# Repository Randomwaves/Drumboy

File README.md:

# Drumboy

**A touch-controlled hardware groovebox** — sequencer, sampler, and DSP effects engine built around an STM32H723 (Cortex-M7), with a 480×854 color display, a fully capacitive-touch control surface, and MIDI/Sync I/O.

This repository holds the complete hardware design (Eagle/KiCad) and firmware (STM32CubeIDE / C++) for Drumboy, released by [Randomwaves](https://randomwaves.io) as an open hardware/software project. Drumboy is the predecessor of [Drumboy Pro](https://github.com/Randomwaves/Drumboy-Pro), sharing the same sequencer and DSP engine on a simpler, touch-based control surface.

---

## Overview

The MCU sits at the center of the same core subsystems as Drumboy Pro: an NT35510 display over a 16-bit parallel GPIO bus, external SDRAM on the FMC bus for sample streaming, an SGTL5000 audio codec over I2S/I2C, a microSD card over SDMMC2 for storage, and MIDI/Sync connectivity over USART/GPIO. In place of mechanical keys and encoders, the control surface is driven entirely by three capacitive-touch channels.

| | |
|---|---|
| **MCU** | STM32H723ZGT6 — Cortex-M7, LQFP-144 |
| **Display** | NT35510, 480×854, 16-bit parallel |
| **SDRAM** | External, FMC bus (sample streaming) |
| **Audio codec** | SGTL5000 — I2S3 audio / I2C3 control |
| **Storage** | microSD, SDMMC2, FAT filesystem |
| **Control surface** | 3× capacitive-touch channels (CT0–CT2) |
| **Connectivity** | MIDI In/Out, Sync In/Out |
| **Firmware** | v1.05 |

## Features

- **10 sample layers**, each with independent LFO-driven modulation
- **Sequencer** with 5 song banks per layer, 64 beats per bank, and algorithmic complex-fill generation (12 sub-hits per fill slot)
- **9 effect types** per send slot: Delay, Chorus, Flanger, Phaser, Compressor, Expander, Overdrive, Distortion, Bitcrusher
- **2 multimode filters + 2 send effects + stereo reverb** in the DSP chain
- **MIDI In/Out** and **Sync In/Out** for external clock/gate sync
- **SD-card firmware updates** via a dedicated bootloader, mirroring the same two-project split as Drumboy Pro

## Repository structure

```
01 Hardware/
  Main/       Main board — Eagle CAD (Main.sch / Main.brd)
  Top/        Top/control-surface board — Eagle CAD (Top.sch / Top.brd)
  Connector/  Interconnect board — KiCad (migrated from Eagle)
  Bottom/     Base board — KiCad (migrated from Eagle)

02 Software/
  Drumboy-Boot-H723/   Bootloader — STM32CubeIDE project
  Drumboy-App-H723/    Application firmware — STM32CubeIDE project
  Firmware/            Prebuilt firmware binaries
  Sd Card/             Reference SD card contents (samples, presets, drumkits, system data)
```

## Hardware

Main and Top were originally designed in **Autodesk Eagle** (`.sch` / `.brd`); Connector and Bottom have since been migrated to **KiCad**.

## Firmware

Built with **STM32CubeIDE**, written in C/C++ against the STM32 HAL. Firmware is split into `Drumboy-Boot-H723` (bootloader) and `Drumboy-App-H723` (application), sharing one flash device — the same split used in Drumboy Pro.

## License

Released under the [MIT License](LICENSE).

## Community

- 💬 [Discord community](https://discord.gg/5atevNH6UU) — join the discussion
- 🌐 [randomwaves.io](https://www.randomwaves.io)
- ✉️ [hello@randomwaves.io](mailto:hello@randomwaves.io)

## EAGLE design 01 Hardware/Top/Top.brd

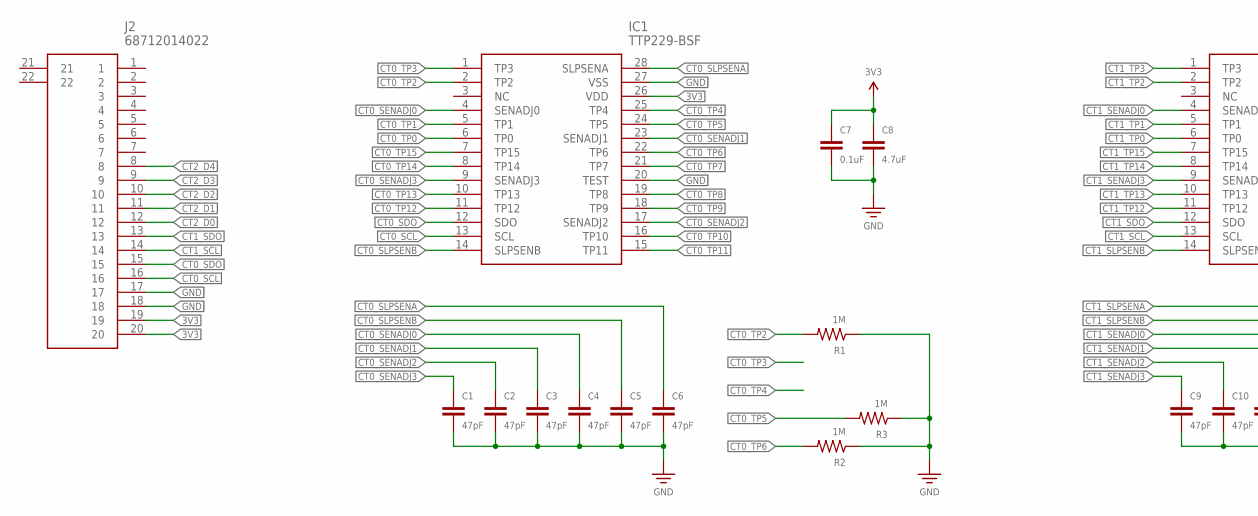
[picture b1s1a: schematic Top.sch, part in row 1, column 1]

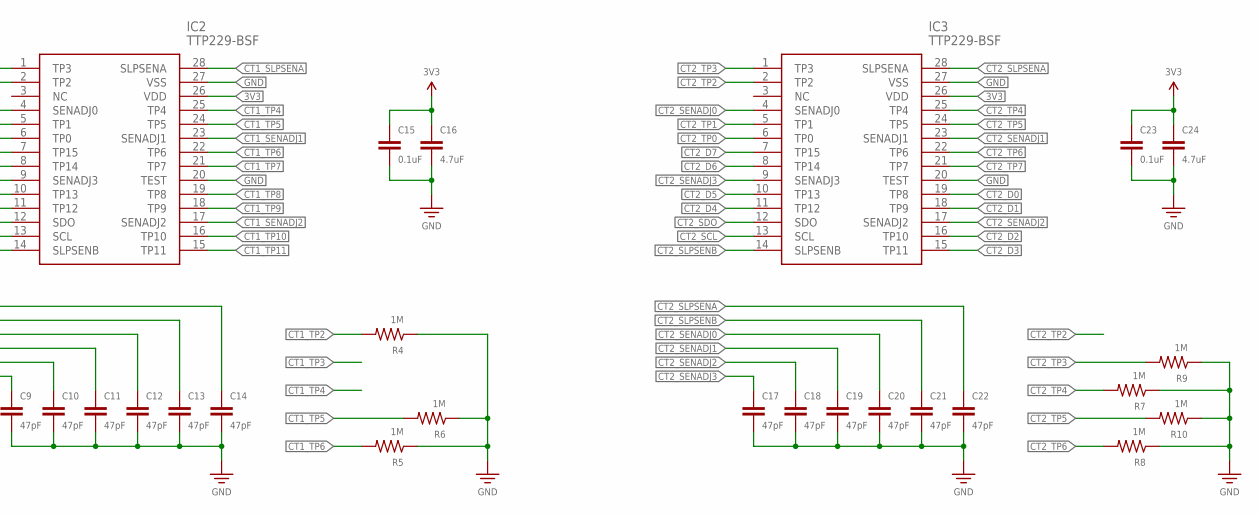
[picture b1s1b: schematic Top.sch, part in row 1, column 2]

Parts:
C1, C2, C3, C4, C5, C6, C9, C10, C11, C12, C13, C14, C17, C18, C19, C20, C21, C22: 47pF; CAP-0603
C7, C15, C23: 0.1uF; CAP-0603
C8, C16, C24: 4.7uF; CAP-0603
IC1, IC2, IC3: TTP229-BSF; SOP64P600X175-28N
J2: 68712014022
R1, R2, R3, R4, R5, R6, R7, R8, R9, R10: 1M; RES-0603

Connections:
3V3: C7.P$1 (1), C8.P$1 (1), C15.P$1 (1), C16.P$1 (1), C23.P$1 (1), C24.P$1 (1), IC1.26 (VDD), IC2.26 (VDD), IC3.26 (VDD), J2.19, J2.20
CT0_SCL: IC1.13 (SCL), J2.16
CT0_SDO: IC1.12 (SDO), J2.15
CT0_SENADJ0: C4.P$1 (1), IC1.4 (SENADJ0)
CT0_SENADJ1: C3.P$1 (1), IC1.23 (SENADJ1)
CT0_SENADJ2: C2.P$1 (1), IC1.17 (SENADJ2)
CT0_SENADJ3: C1.P$1 (1), IC1.9 (SENADJ3)
CT0_SLPSENA: C6.P$1 (1), IC1.28 (SLPSENA)
CT0_SLPSENB: C5.P$1 (1), IC1.14 (SLPSENB)
CT0_TP0: IC1.6 (TP0)
CT0_TP1: IC1.5 (TP1)
CT0_TP2: IC1.2 (TP2), R1.P$2 (2)
CT0_TP3: IC1.1 (TP3)
CT0_TP4: IC1.25 (TP4)
CT0_TP5: IC1.24 (TP5), R3.P$2 (2)
CT0_TP6: IC1.22 (TP6), R2.P$2 (2)
CT0_TP7: IC1.21 (TP7)
CT0_TP8: IC1.19 (TP8)
CT0_TP9: IC1.18 (TP9)
CT0_TP10: IC1.16 (TP10)
CT0_TP11: IC1.15 (TP11)
CT0_TP12: IC1.11 (TP12)
CT0_TP13: IC1.10 (TP13)
CT0_TP14: IC1.8 (TP14)
CT0_TP15: IC1.7 (TP15)
CT1_SCL: IC2.13 (SCL), J2.14
CT1_SDO: IC2.12 (SDO), J2.13
CT1_SENADJ0: C12.P$1 (1), IC2.4 (SENADJ0)
CT1_SENADJ1: C11.P$1 (1), IC2.23 (SENADJ1)
CT1_SENADJ2: C10.P$1 (1), IC2.17 (SENADJ2)
CT1_SENADJ3: C9.P$1 (1), IC2.9 (SENADJ3)
CT1_SLPSENA: C14.P$1 (1), IC2.28 (SLPSENA)
CT1_SLPSENB: C13.P$1 (1), IC2.14 (SLPSENB)
CT1_TP0: IC2.6 (TP0)
CT1_TP1: IC2.5 (TP1)
CT1_TP2: IC2.2 (TP2), R4.P$2 (2)
CT1_TP3: IC2.1 (TP3)
CT1_TP4: IC2.25 (TP4)
CT1_TP5: IC2.24 (TP5), R6.P$2 (2)
CT1_TP6: IC2.22 (TP6), R5.P$2 (2)
CT1_TP7: IC2.21 (TP7)
CT1_TP8: IC2.19 (TP8)
CT1_TP9: IC2.18 (TP9)
CT1_TP10: IC2.16 (TP10)
CT1_TP11: IC2.15 (TP11)
CT1_TP12: IC2.11 (TP12)
CT1_TP13: IC2.10 (TP13)
CT1_TP14: IC2.8 (TP14)
CT1_TP15: IC2.7 (TP15)
CT2_D0: IC3.19 (TP8), J2.12
CT2_D1: IC3.18 (TP9), J2.11
CT2_D2: IC3.16 (TP10), J2.10
CT2_D3: IC3.15 (TP11), J2.9
CT2_D4: IC3.11 (TP12), J2.8
CT2_D5: IC3.10 (TP13)
CT2_D6: IC3.8 (TP14)
CT2_D7: IC3.7 (TP15)
CT2_SCL: IC3.13 (SCL)
CT2_SDO: IC3.12 (SDO)
CT2_SENADJ0: C20.P$1 (1), IC3.4 (SENADJ0)
CT2_SENADJ1: C19.P$1 (1), IC3.23 (SENADJ1)
CT2_SENADJ2: C18.P$1 (1), IC3.17 (SENADJ2)
CT2_SENADJ3: C17.P$1 (1), IC3.9 (SENADJ3)
CT2_SLPSENA: C22.P$1 (1), IC3.28 (SLPSENA)
CT2_SLPSENB: C21.P$1 (1), IC3.14 (SLPSENB)
CT2_TP0: IC3.6 (TP0)
CT2_TP1: IC3.5 (TP1)
CT2_TP2: IC3.2 (TP2)
CT2_TP3: IC3.1 (TP3), R9.P$2 (2)
CT2_TP4: IC3.25 (TP4), R7.P$2 (2)
CT2_TP5: IC3.24 (TP5), R10.P$2 (2)
CT2_TP6: IC3.22 (TP6), R8.P$2 (2)
CT2_TP7: IC3.21 (TP7)
GND: C1.P$2 (2), C2.P$2 (2), C3.P$2 (2), C4.P$2 (2), C5.P$2 (2), C6.P$2 (2), C7.P$2 (2), C8.P$2 (2), C9.P$2 (2), C10.P$2 (2), C11.P$2 (2), C12.P$2 (2), C13.P$2 (2), C14.P$2 (2), C15.P$2 (2), C16.P$2 (2), C17.P$2 (2), C18.P$2 (2), C19.P$2 (2), C20.P$2 (2), C21.P$2 (2), C22.P$2 (2), C23.P$2 (2), C24.P$2 (2), IC1.20 (TEST), IC1.27 (VSS), IC2.20 (TEST), IC2.27 (VSS), IC3.20 (TEST), IC3.27 (VSS), J2.17, J2.18, R1.P$1 (1), R2.P$1 (1), R3.P$1 (1), R4.P$1 (1), R5.P$1 (1), R6.P$1 (1), R7.P$1 (1), R8.P$1 (1), R9.P$1 (1), R10.P$1 (1)

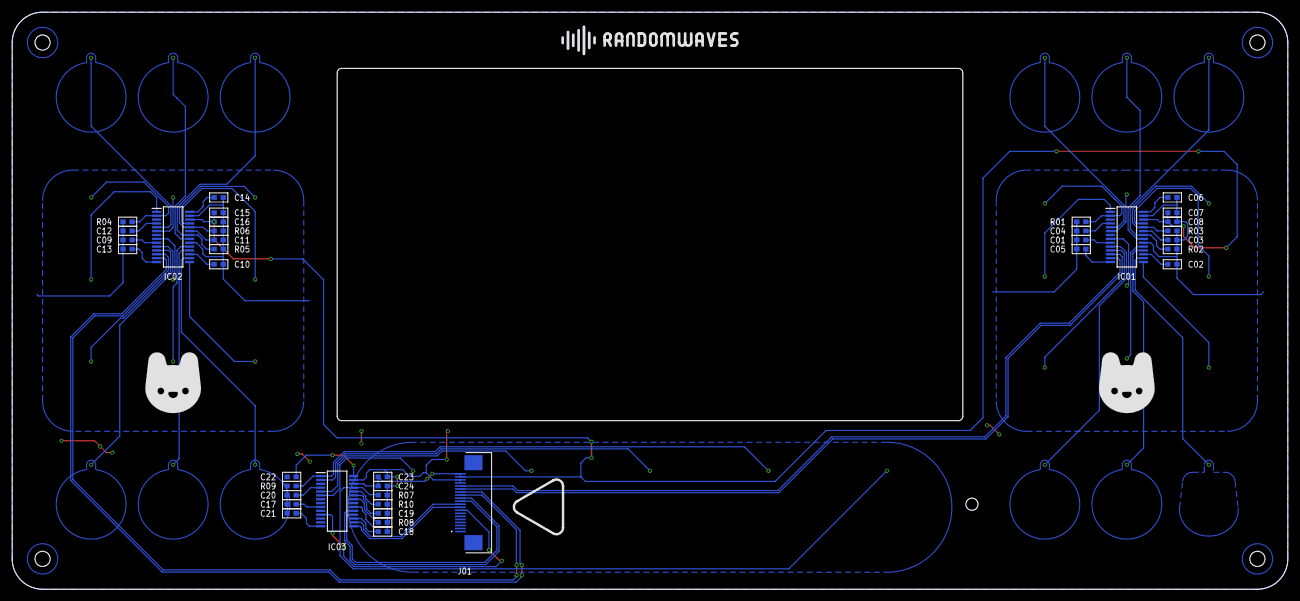
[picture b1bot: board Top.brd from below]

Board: 2 copper layers, 210.0 x 95.0 mm, 38 parts (38 on the bottom side), 39 nets.

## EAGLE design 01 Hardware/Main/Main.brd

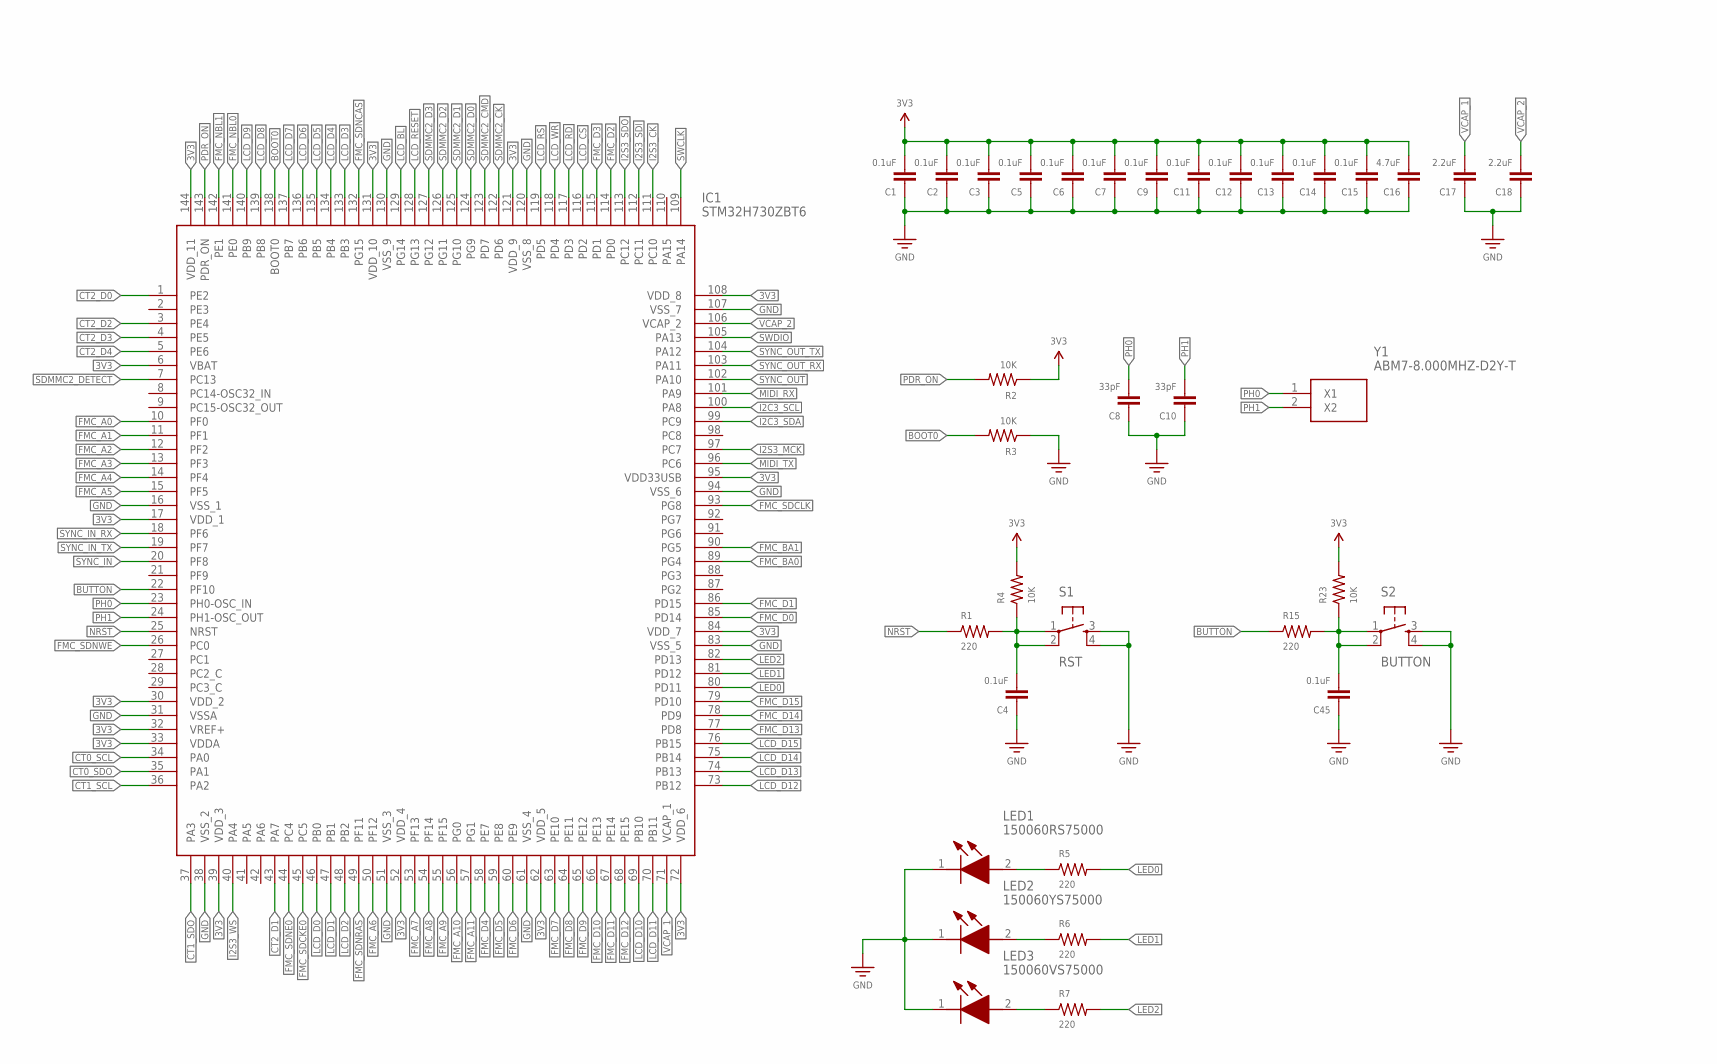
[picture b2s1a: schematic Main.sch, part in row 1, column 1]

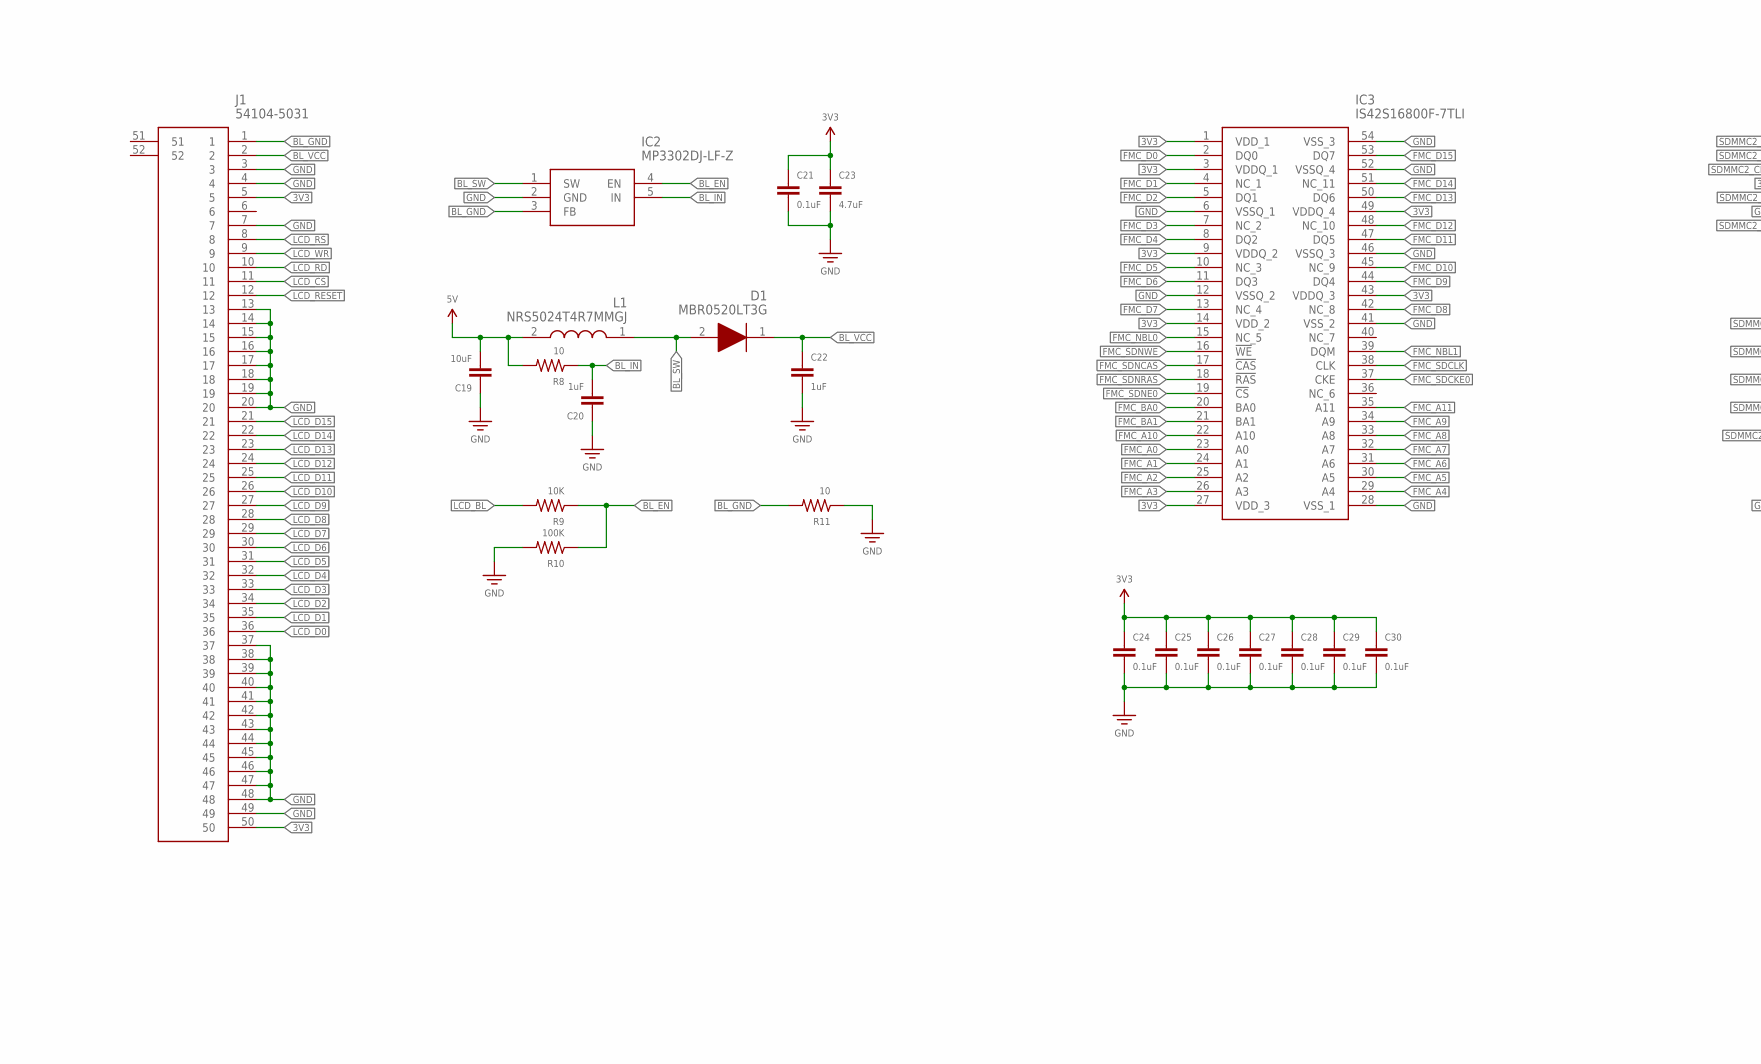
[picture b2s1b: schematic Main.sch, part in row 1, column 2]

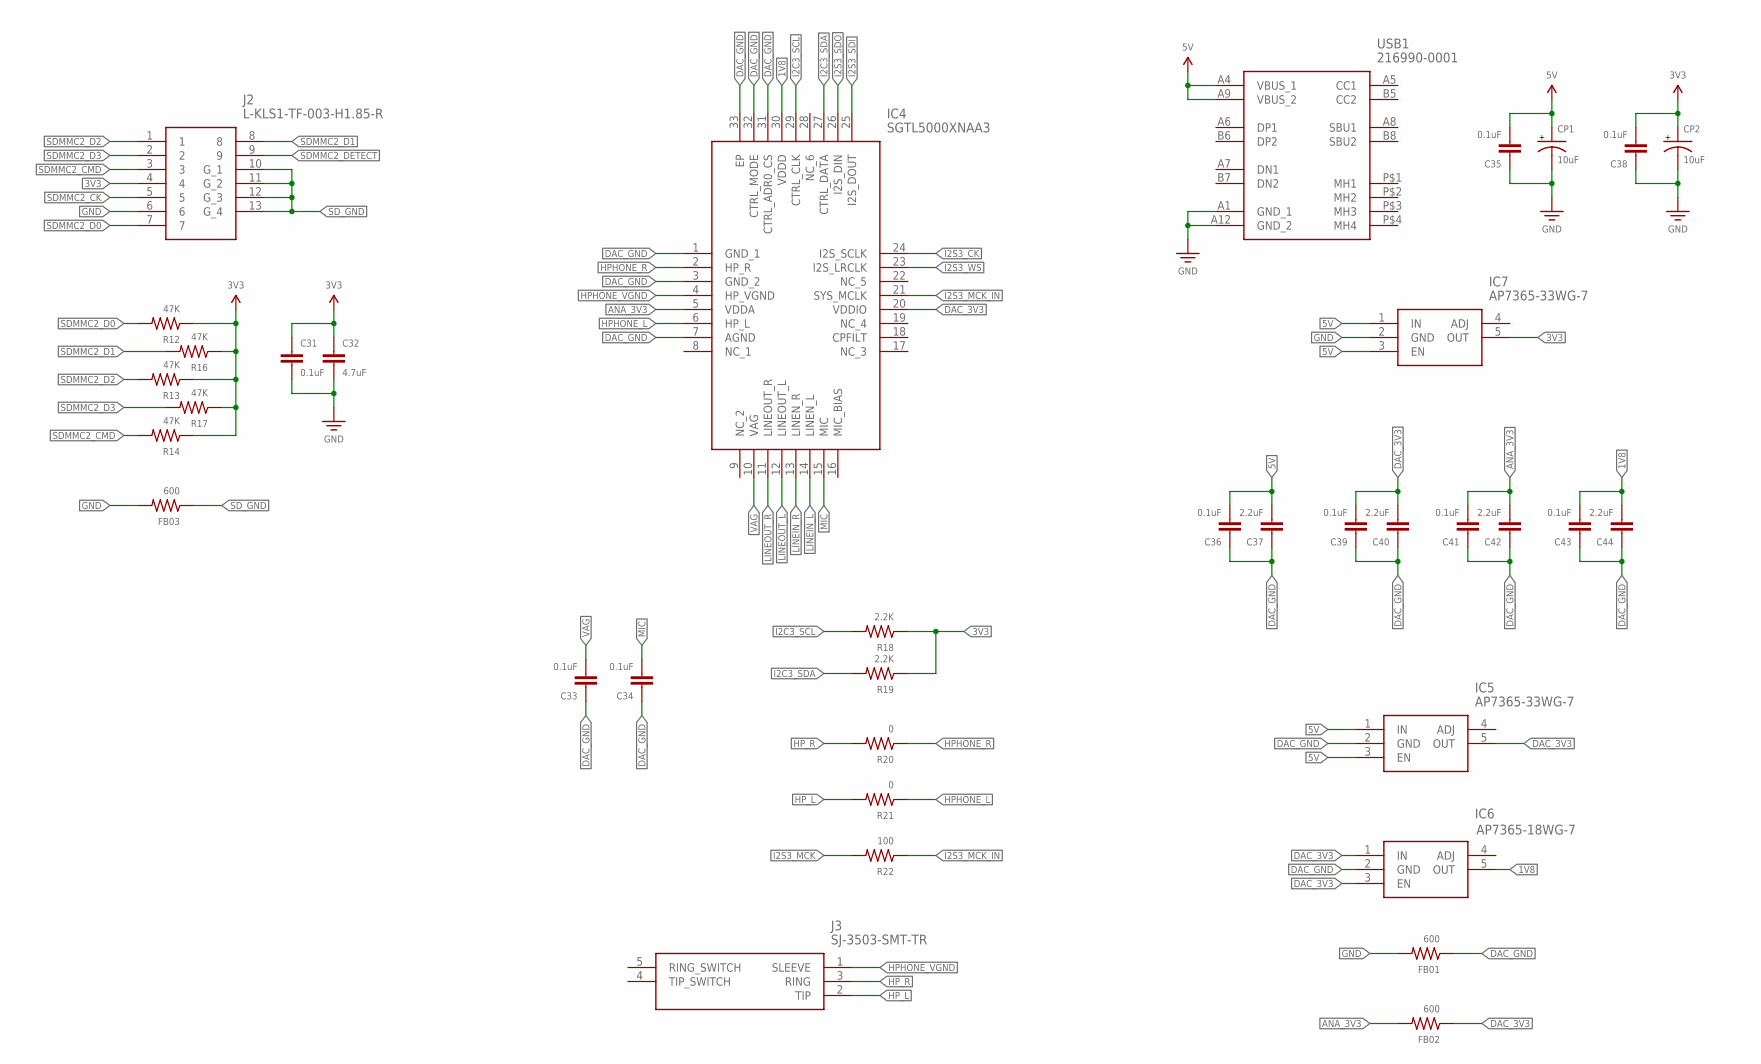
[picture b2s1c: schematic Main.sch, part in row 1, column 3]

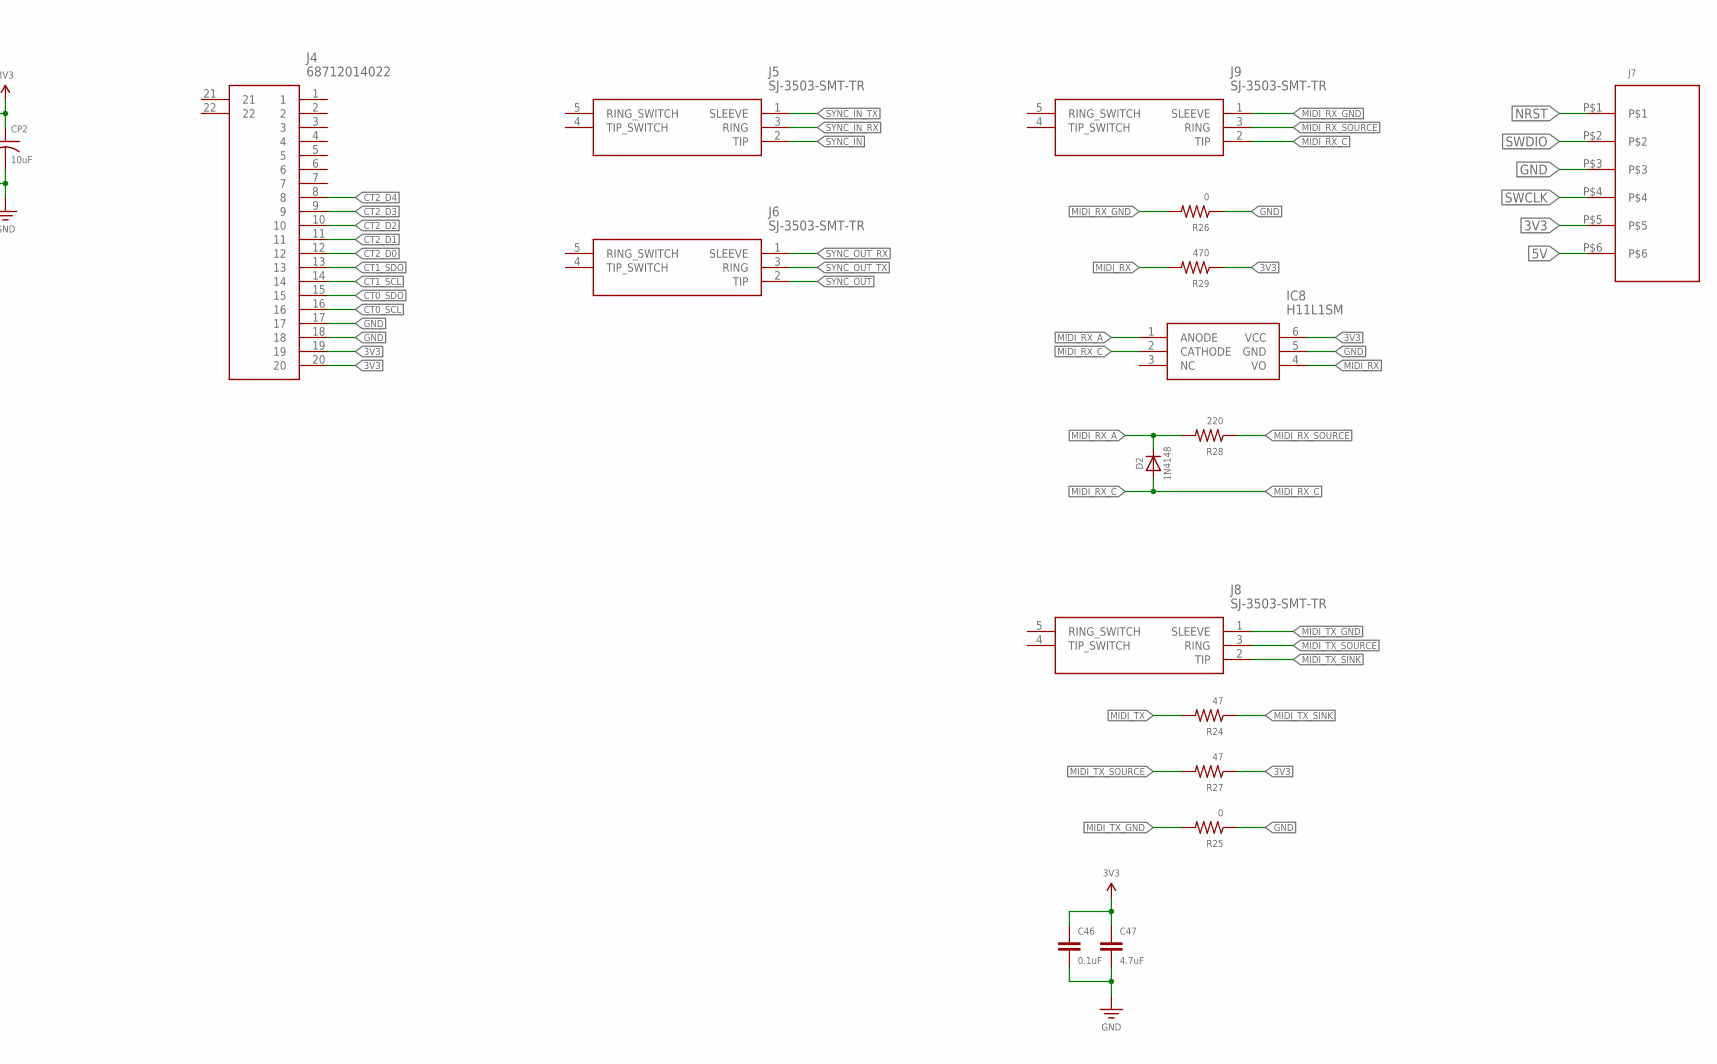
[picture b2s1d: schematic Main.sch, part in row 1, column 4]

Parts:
C1, C2, C3, C4, C5, C6, C7, C9, C11, C12, C13, C14, C15, C21, C24, C25, C26, C27, C28, C29, C30, C31, C33, C34, C35, C36, C38, C39, C41, C43, C45, C46: 0.1uF; CAP-0603
C8, C10: 33pF; CAP-0603
C16, C23, C32, C47: 4.7uF; CAP-0603
C17, C18, C37, C40, C42, C44: 2.2uF; CAP-0603
C19: 10uF; CAP-0603
C20, C22: 1uF; CAP-0603
CP1, CP2: 10uF; CAP-POL-1206
D1: MBR0520LT3G; SOD3716X135N
D2: 1N4148; SOD-323
FB01, FB02, FB03: 600; RES-0603
IC1: STM32H730ZBT6; QFP50P2200X2200X160-144N
IC2: MP3302DJ-LF-Z; SOT95P280X100-5N
IC3: IS42S16800F-7TLI; SOP80P1176X120-54N
IC4: SGTL5000XNAA3; QFN50P500X500X90-33N
IC5, IC7: AP7365-33WG-7; SOT95P285X130-5N
IC6: AP7365-18WG-7; SOT95P285X130-5N
IC8: H11L1SM; SMT-6PIN-(LEAD-BEND)
J1: 54104-5031; 541045031
J2: L-KLS1-TF-003-H1.85-R
J3, J5, J6, J8, J9: SJ-3503-SMT-TR; SJ3503SMTTR
J4: 68712014022
J7: HFW6R-2STE1LF
L1: NRS5024T4R7MMGJ
LED1: 150060RS75000; LEDC1608X80N
LED2: 150060YS75000; LEDC1608X80N
LED3: 150060VS75000; LEDC1608X80N
R1, R5, R6, R7, R15, R28: 220; RES-0603
R2, R3, R4, R9, R23: 10K; RES-0603
R8, R11: 10; RES-0603
R10: 100K; RES-0603
R12, R13, R14, R16, R17: 47K; RES-0603
R18, R19: 2.2K; RES-0603
R20, R21, R25, R26: 0; RES-0603
R22: 100; RES-0603
R24, R27: 47; RES-0603
R29: 470; RES-0603
S1: RST; TACTILE-SWITCH-SMD
S2: BUTTON; TACTILE-SWITCH-SMD
USB1: 216990-0001; 2169900001
Y1: ABM7-8.000MHZ-D2Y-T; ABM78000MHZD2YT

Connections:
1V8: C43.P$2 (2), C44.P$2 (2), IC4.30 (VDDD), IC6.5 (OUT)
3V3: C1.P$2 (2), C2.P$2 (2), C3.P$2 (2), C5.P$2 (2), C6.P$2 (2), C7.P$2 (2), C9.P$2 (2), C11.P$2 (2), C12.P$2 (2), C13.P$2 (2), C14.P$2 (2), C15.P$2 (2), C16.P$2 (2), C21.P$1 (1), C23.P$1 (1), C24.P$1 (1), C25.P$1 (1), C26.P$1 (1), C27.P$1 (1), C28.P$1 (1), C29.P$1 (1), C30.P$1 (1), C31.P$1 (1), C32.P$1 (1), C38.P$2 (2), C46.P$1 (1), C47.P$1 (1), CP2.P$1 (+), IC1.6 (VBAT), IC1.17 (VDD_1), IC1.30 (VDD_2), IC1.32 (VREF+), IC1.33 (VDDA), IC1.39 (VDD_3), IC1.52 (VDD_4), IC1.62 (VDD_5), IC1.72 (VDD_6), IC1.84 (VDD_7), IC1.95 (VDD33USB), IC1.108 (VDD_8), IC1.121 (VDD_9), IC1.131 (VDD_10), IC1.144 (VDD_11), IC3.1 (VDD_1), IC3.3 (VDDQ_1), IC3.9 (VDDQ_2), IC3.14 (VDD_2), IC3.27 (VDD_3), IC3.43 (VDDQ_3), IC3.49 (VDDQ_4), IC7.5 (OUT), IC8.6 (VCC), J1.5, J1.50, J2.4, J4.19, J4.20, J7.P$5, R2.P$1 (1), R4.P$2 (2), R12.P$1 (1), R13.P$1 (1), R14.P$1 (1), R16.P$1 (1), R17.P$1 (1), R18.P$1 (1), R19.P$1 (1), R23.P$2 (2), R27.P$1 (1), R29.P$1 (1)
5V: C19.P$2 (2), C35.P$2 (2), C36.P$2 (2), C37.P$2 (2), CP1.P$1 (+), IC5.1 (IN), IC5.3 (EN), IC7.1 (IN), IC7.3 (EN), J7.P$6, L1.2, R8.P$2 (2), USB1.A4 (VBUS_1), USB1.A9 (VBUS_2)
ANA_3V3: C41.P$2 (2), C42.P$2 (2), FB02.P$2 (2), IC4.5 (VDDA)
BL_EN: IC2.4 (EN), R9.P$1 (1), R10.P$1 (1)
BL_GND: IC2.3 (FB), J1.1, R11.P$2 (2)
BL_IN: C20.P$2 (2), IC2.5 (IN), R8.P$1 (1)
BL_SW: D1.2 (A), IC2.1 (SW), L1.1
BL_VCC: C22.P$1 (1), D1.1 (K), J1.2
BOOT0: IC1.138 (BOOT0), R3.P$2 (2)
BUTTON: IC1.22 (PF10), R15.P$1 (1)
CT0_SCL: IC1.34 (PA0), J4.16
CT0_SDO: IC1.35 (PA1), J4.15
CT1_SCL: IC1.36 (PA2), J4.14
CT1_SDO: IC1.37 (PA3), J4.13
CT2_D0: IC1.1 (PE2), J4.12
CT2_D1: IC1.43 (PA7), J4.11
CT2_D2: IC1.3 (PE4), J4.10
CT2_D3: IC1.4 (PE5), J4.9
CT2_D4: IC1.5 (PE6), J4.8
DAC_3V3: C39.P$2 (2), C40.P$2 (2), FB02.P$1 (1), IC4.20 (VDDIO), IC5.5 (OUT), IC6.1 (IN), IC6.3 (EN)
DAC_GND: C33.P$1 (1), C34.P$1 (1), C36.P$1 (1), C37.P$1 (1), C39.P$1 (1), C40.P$1 (1), C41.P$1 (1), C42.P$1 (1), C43.P$1 (1), C44.P$1 (1), FB01.P$1 (1), IC4.1 (GND_1), IC4.3 (GND_2), IC4.7 (AGND), IC4.31 (CTRL_ADR0_CS), IC4.32 (CTRL_MODE), IC4.33 (EP), IC5.2 (GND), IC6.2 (GND)
FMC_A0: IC1.10 (PF0), IC3.23 (A0)
FMC_A1: IC1.11 (PF1), IC3.24 (A1)
FMC_A2: IC1.12 (PF2), IC3.25 (A2)
FMC_A3: IC1.13 (PF3), IC3.26 (A3)
FMC_A4: IC1.14 (PF4), IC3.29 (A4)
FMC_A5: IC1.15 (PF5), IC3.30 (A5)
FMC_A6: IC1.50 (PF12), IC3.31 (A6)
FMC_A7: IC1.53 (PF13), IC3.32 (A7)
FMC_A8: IC1.54 (PF14), IC3.33 (A8)
FMC_A9: IC1.55 (PF15), IC3.34 (A9)
FMC_A10: IC1.56 (PG0), IC3.22 (A10)
FMC_A11: IC1.57 (PG1), IC3.35 (A11)
FMC_BA0: IC1.89 (PG4), IC3.20 (BA0)
FMC_BA1: IC1.90 (PG5), IC3.21 (BA1)
FMC_D0: IC1.85 (PD14), IC3.2 (DQ0)
FMC_D1: IC1.86 (PD15), IC3.4 (NC_1)
FMC_D2: IC1.114 (PD0), IC3.5 (DQ1)
FMC_D3: IC1.115 (PD1), IC3.7 (NC_2)
FMC_D4: IC1.58 (PE7), IC3.8 (DQ2)
FMC_D5: IC1.59 (PE8), IC3.10 (NC_3)
FMC_D6: IC1.60 (PE9), IC3.11 (DQ3)
FMC_D7: IC1.63 (PE10), IC3.13 (NC_4)
FMC_D8: IC1.64 (PE11), IC3.42 (NC_8)
FMC_D9: IC1.65 (PE12), IC3.44 (DQ4)
FMC_D10: IC1.66 (PE13), IC3.45 (NC_9)
FMC_D11: IC1.67 (PE14), IC3.47 (DQ5)
FMC_D12: IC1.68 (PE15), IC3.48 (NC_10)
FMC_D13: IC1.77 (PD8), IC3.50 (DQ6)
FMC_D14: IC1.78 (PD9), IC3.51 (NC_11)
FMC_D15: IC1.79 (PD10), IC3.53 (DQ7)
FMC_NBL0: IC1.141 (PE0), IC3.15 (NC_5)
FMC_NBL1: IC1.142 (PE1), IC3.39 (DQM)
FMC_SDCKE0: IC1.45 (PC5), IC3.37 (CKE)
FMC_SDCLK: IC1.93 (PG8), IC3.38 (CLK)
FMC_SDNCAS: IC1.132 (PG15), IC3.17 (!CAS)
FMC_SDNE0: IC1.44 (PC4), IC3.19 (!CS)
FMC_SDNRAS: IC1.49 (PF11), IC3.18 (!RAS)
FMC_SDNWE: IC1.26 (PC0), IC3.16 (!WE)
GND: C1.P$1 (1), C2.P$1 (1), C3.P$1 (1), C4.P$1 (1), C5.P$1 (1), C6.P$1 (1), C7.P$1 (1), C8.P$1 (1), C9.P$1 (1), C10.P$1 (1), C11.P$1 (1), C12.P$1 (1), C13.P$1 (1), C14.P$1 (1), C15.P$1 (1), C16.P$1 (1), C17.P$1 (1), C18.P$1 (1), C19.P$1 (1), C20.P$1 (1), C21.P$2 (2), C22.P$2 (2), C23.P$2 (2), C24.P$2 (2), C25.P$2 (2), C26.P$2 (2), C27.P$2 (2), C28.P$2 (2), C29.P$2 (2), C30.P$2 (2), C31.P$2 (2), C32.P$2 (2), C35.P$1 (1), C38.P$1 (1), C45.P$1 (1), C46.P$2 (2), C47.P$2 (2), CP1.P$2 (-), CP2.P$2 (-), FB01.P$2 (2), FB03.P$2 (2), IC1.16 (VSS_1), IC1.31 (VSSA), IC1.38 (VSS_2), IC1.51 (VSS_3), IC1.61 (VSS_4), IC1.83 (VSS_5), IC1.94 (VSS_6), IC1.107 (VSS_7), IC1.120 (VSS_8), IC1.130 (VSS_9), IC2.2 (GND), IC3.6 (VSSQ_1), IC3.12 (VSSQ_2), IC3.28 (VSS_1), IC3.41 (VSS_2), IC3.46 (VSSQ_3), IC3.52 (VSSQ_4), IC3.54 (VSS_3), IC7.2 (GND), IC8.5 (GND), J1.3, J1.4, J1.7, J1.13, J1.14, J1.15, J1.16, J1.17, J1.18, J1.19, J1.20, J1.37, J1.38, J1.39, J1.40, J1.41, J1.42, J1.43, J1.44, J1.45, J1.46, J1.47, J1.48, J1.49, J2.6, J4.17, J4.18, J7.P$3, LED1.1 (K), LED2.1 (K), LED3.1 (K), R3.P$1 (1), R10.P$2 (2), R11.P$1 (1), R25.P$1 (1), R26.P$1 (1), S1.3, S1.4, S2.3, S2.4, USB1.A1 (GND_1), USB1.A12 (GND_2)
HPHONE_L: IC4.6 (HP_L), R21.P$1 (1)
HPHONE_R: IC4.2 (HP_R), R20.P$1 (1)
HPHONE_VGND: IC4.4 (HP_VGND), J3.1 (SLEEVE)
HP_L: J3.2 (TIP), R21.P$2 (2)
HP_R: J3.3 (RING), R20.P$2 (2)
I2C3_SCL: IC1.100 (PA8), IC4.29 (CTRL_CLK), R18.P$2 (2)
I2C3_SDA: IC1.99 (PC9), IC4.27 (CTRL_DATA), R19.P$2 (2)
I2S3_CK: IC1.111 (PC10), IC4.24 (I2S_SCLK)
I2S3_MCK: IC1.97 (PC7), R22.P$2 (2)
I2S3_MCK_IN: IC4.21 (SYS_MCLK), R22.P$1 (1)
I2S3_SDI: IC1.112 (PC11), IC4.25 (I2S_DOUT)
I2S3_SDO: IC1.113 (PC12), IC4.26 (I2S_DIN)
I2S3_WS: IC1.40 (PA4), IC4.23 (I2S_LRCLK)
LCD_BL: IC1.129 (PG14), R9.P$2 (2)
LCD_CS: IC1.116 (PD2), J1.11
LCD_D0: IC1.46 (PB0), J1.36
LCD_D1: IC1.47 (PB1), J1.35
LCD_D2: IC1.48 (PB2), J1.34
LCD_D3: IC1.133 (PB3), J1.33
LCD_D4: IC1.134 (PB4), J1.32
LCD_D5: IC1.135 (PB5), J1.31
LCD_D6: IC1.136 (PB6), J1.30
LCD_D7: IC1.137 (PB7), J1.29
LCD_D8: IC1.139 (PB8), J1.28
LCD_D9: IC1.140 (PB9), J1.27
LCD_D10: IC1.69 (PB10), J1.26
LCD_D11: IC1.70 (PB11), J1.25
LCD_D12: IC1.73 (PB12), J1.24
LCD_D13: IC1.74 (PB13), J1.23
LCD_D14: IC1.75 (PB14), J1.22
LCD_D15: IC1.76 (PB15), J1.21
LCD_RD: IC1.117 (PD3), J1.10
LCD_RESET: IC1.128 (PG13), J1.12
LCD_RS: IC1.119 (PD5), J1.8
LCD_WR: IC1.118 (PD4), J1.9
LED0: IC1.80 (PD11), R5.P$2 (2)
LED1: IC1.81 (PD12), R6.P$2 (2)
LED2: IC1.82 (PD13), R7.P$2 (2)
LINEIN_L: IC4.14 (LINEN_L)
LINEIN_R: IC4.13 (LINEN_R)
LINEOUT_L: IC4.12 (LINEOUT_L)
LINEOUT_R: IC4.11 (LINEOUT_R)
MIC: C34.P$2 (2), IC4.15 (MIC)
MIDI_RX: IC1.101 (PA9), IC8.4 (VO), R29.P$2 (2)
MIDI_RX_A: D2.C, IC8.1 (ANODE), R28.P$2 (2)
MIDI_RX_C: D2.A, IC8.2 (CATHODE), J9.2 (TIP)
MIDI_RX_GND: J9.1 (SLEEVE), R26.P$2 (2)
MIDI_RX_SOURCE: J9.3 (RING), R28.P$1 (1)
MIDI_TX: IC1.96 (PC6), R24.P$2 (2)
MIDI_TX_GND: J8.1 (SLEEVE), R25.P$2 (2)
MIDI_TX_SINK: J8.2 (TIP), R24.P$1 (1)
MIDI_TX_SOURCE: J8.3 (RING), R27.P$2 (2)
unnamed: C45.P$2 (2), R15.P$2 (2), R23.P$1 (1), S2.1, S2.2
unnamed: C4.P$2 (2), R1.P$2 (2), R4.P$1 (1), S1.1, S1.2
unnamed: LED1.2 (A), R5.P$1 (1)
unnamed: LED2.2 (A), R6.P$1 (1)
unnamed: LED3.2 (A), R7.P$1 (1)
NRST: IC1.25 (NRST), J7.P$1, R1.P$1 (1)
PDR_ON: IC1.143 (PDR_ON), R2.P$2 (2)
PH0: C8.P$2 (2), IC1.23 (PH0-OSC_IN), Y1.1 (X1)
PH1: C10.P$2 (2), IC1.24 (PH1-OSC_OUT), Y1.2 (X2)
SDMMC2_CK: IC1.122 (PD6), J2.5
SDMMC2_CMD: IC1.123 (PD7), J2.3, R14.P$2 (2)
SDMMC2_D0: IC1.124 (PG9), J2.7, R12.P$2 (2)
SDMMC2_D1: IC1.125 (PG10), J2.8, R16.P$2 (2)
SDMMC2_D2: IC1.126 (PG11), J2.1, R13.P$2 (2)
SDMMC2_D3: IC1.127 (PG12), J2.2, R17.P$2 (2)
SDMMC2_DETECT: IC1.7 (PC13), J2.9
SD_GND: FB03.P$1 (1), J2.10 (G_1), J2.11 (G_2), J2.12 (G_3), J2.13 (G_4)
SWCLK: IC1.109 (PA14), J7.P$4
SWDIO: IC1.105 (PA13), J7.P$2
SYNC_IN: IC1.20 (PF8), J5.2 (TIP)
SYNC_IN_RX: IC1.18 (PF6), J5.3 (RING)
SYNC_IN_TX: IC1.19 (PF7), J5.1 (SLEEVE)
SYNC_OUT: IC1.102 (PA10), J6.2 (TIP)
SYNC_OUT_RX: IC1.103 (PA11), J6.1 (SLEEVE)
SYNC_OUT_TX: IC1.104 (PA12), J6.3 (RING)
VAG: C33.P$2 (2), IC4.10 (VAG)
VCAP_1: C17.P$2 (2), IC1.71 (VCAP_1)
VCAP_2: C18.P$2 (2), IC1.106 (VCAP_2)

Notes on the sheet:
AP7365-18WG-7

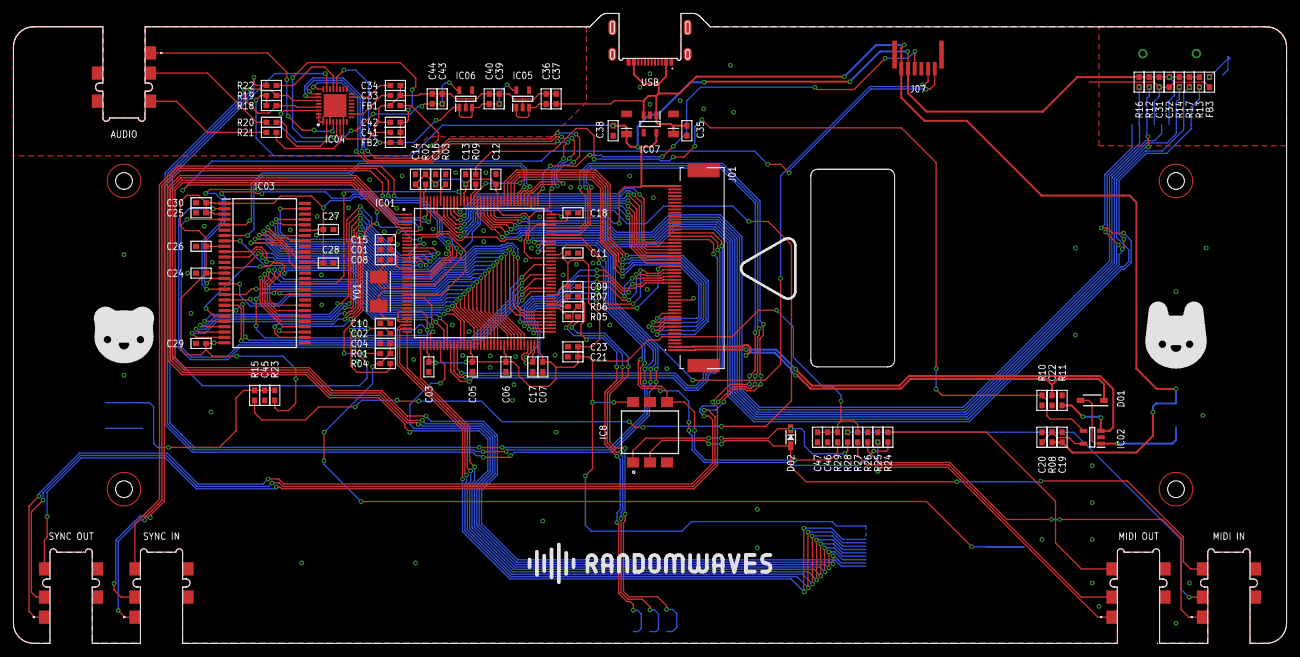
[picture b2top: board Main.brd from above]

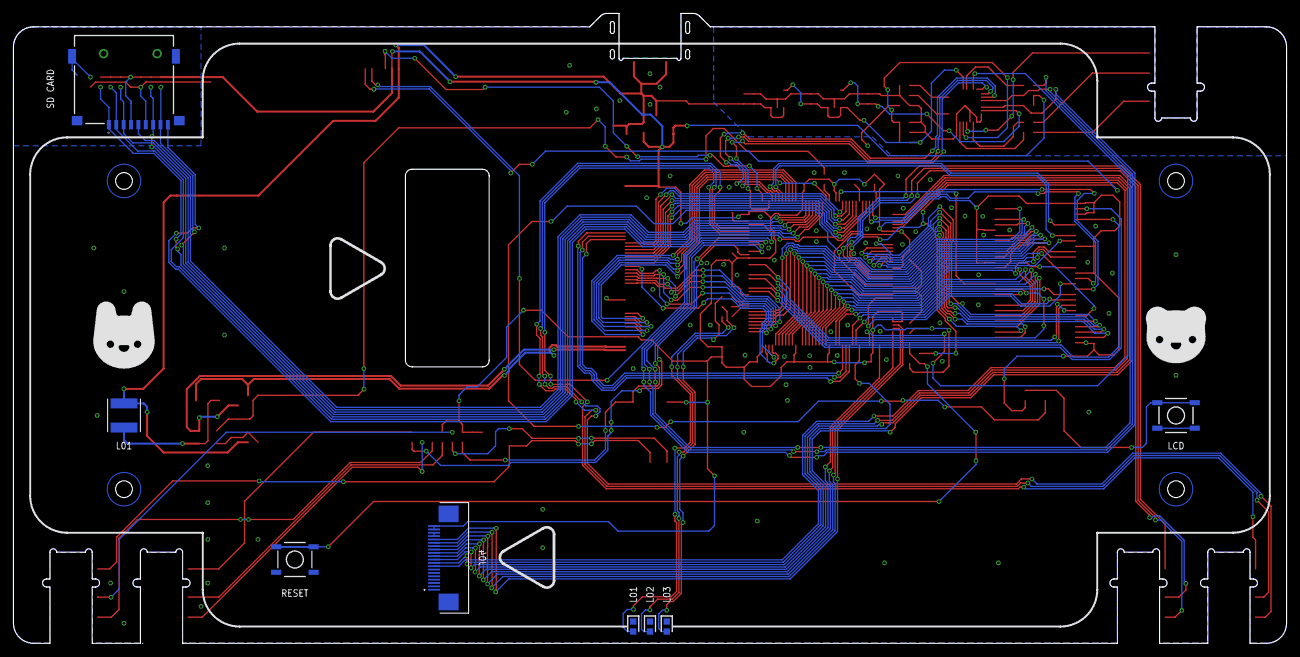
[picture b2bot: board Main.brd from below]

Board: 2 copper layers, 190.0 x 94.0 mm, 108 parts (8 on the bottom side), 137 nets.

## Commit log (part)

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2025-04-04 Release v1.01
2025-04-28 Controller.cpp: Respect NoteOn with Velocity=0 as NoteOff
    A lot of midi keyboards, (Novaton LaunchKey MK3 mini for example)
    send a NoteOn with Velocity=0 as a NoteOff. Current Drumboy firmware
    seems to expect a NoteOff, but as a NoteOff never occurs, the note just
    keeps playing.
    This is an untested patch (need the STLink etc) but it should in theory
    fix things.

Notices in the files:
parts and their libraries:
SparkFun-Electromechanical: Licensing: Creative Commons ShareAlike 4.0 International - https://creativecommons.org/licenses/by-sa/4.0
microbuilder: This work is placed in the public domain, and may be freely used for commercial and non-commercial work with the following conditions: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
